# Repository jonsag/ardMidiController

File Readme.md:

# ardMidiController

## Links

### theMidinator

[YouTube](https://www.youtube.com/watch?v=JZ5yPdoPooU)  
[GitHub](https://github.com/SwitchAndLever/theMIDInatorxxx)

### SimpleSynth

### dolcewang

[Instructables](https://www.instructables.com/DIY-USB-Midi-Controller-With-Arduino-a-Beginners-G/)

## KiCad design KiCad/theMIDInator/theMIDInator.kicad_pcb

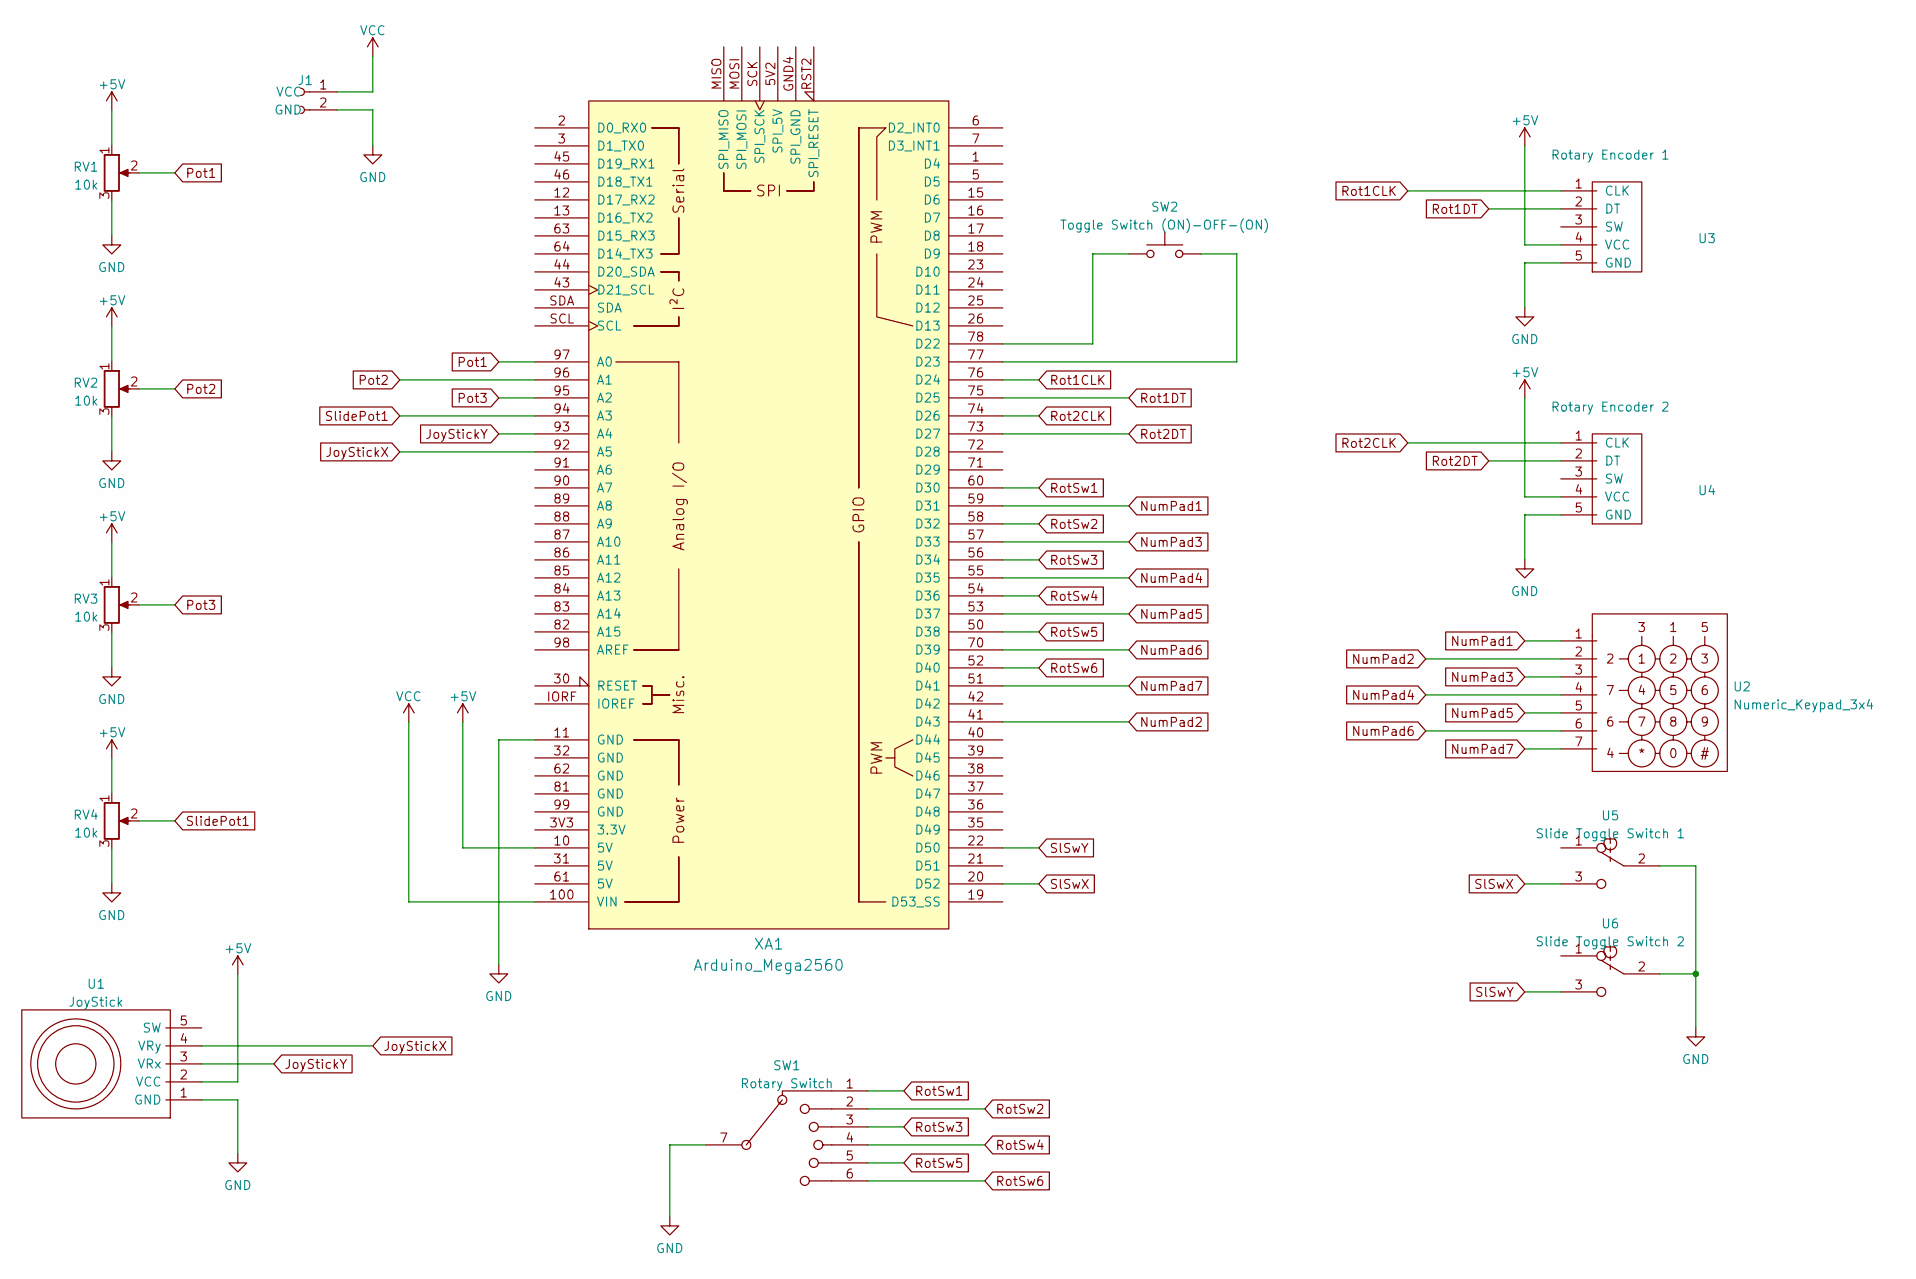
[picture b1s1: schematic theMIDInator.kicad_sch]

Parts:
J1: 2-pin_power_input_header
RV1, RV2, RV3, RV4: 10k; 3-pin JST Potentiometer
SW1: Rotary Switch; 7-pin JST Rotary Switch 1x6
SW2: Toggle Switch (ON)-OFF-(ON); 2-pin JST Switch
U1: JoyStick; 5-pin JST KY-023 JoyStick
U2: Numeric_Keypad_3x4; 7-pin JST Numeric Keypad
U3: Rotary Encoder 1; 5-pin JST Rotary Encoder
U4: Rotary Encoder 2; 5-pin JST Rotary Encoder
U5: Slide Toggle Switch 1; 3-pin JST Toggle Switch
U6: Slide Toggle Switch 2; 3-pin JST Toggle Switch
XA1: Arduino_Mega2560; Arduino_Mega2560_Shield__no_ICSP_no_mount-holes_large

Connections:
+5V: RV1.1, RV2.1, RV3.1, RV4.1, U1.2 (VCC), U3.4 (VCC), U4.4 (VCC), XA1.10 (5V)
GND: J1.2 (GND), RV1.3, RV2.3, RV3.3, RV4.3, SW1.7, U1.1 (GND), U3.5 (GND), U4.5 (GND), U5.2 (Com), U6.2 (Com), XA1.11 (GND)
JoyStickX: U1.4 (VRy), XA1.92 (A5)
JoyStickY: U1.3 (VRx), XA1.93 (A4)
unnamed: SW2.1, XA1.78 (D22)
unnamed: SW2.2, XA1.77 (D23)
NumPad1: U2.1, XA1.59 (D31)
NumPad2: U2.2, XA1.41 (D43)
NumPad3: U2.3, XA1.57 (D33)
NumPad4: U2.4, XA1.55 (D35)
NumPad5: U2.5, XA1.53 (D37)
NumPad6: U2.6, XA1.70 (D39)
NumPad7: U2.7, XA1.51 (D41)
Pot1: RV1.2, XA1.97 (A0)
Pot2: RV2.2, XA1.96 (A1)
Pot3: RV3.2, XA1.95 (A2)
Rot1CLK: U3.1 (CLK), XA1.76 (D24)
Rot1DT: U3.2 (DT), XA1.75 (D25)
Rot2CLK: U4.1 (CLK), XA1.74 (D26)
Rot2DT: U4.2 (DT), XA1.73 (D27)
RotSw1: SW1.1, XA1.60 (D30)
RotSw2: SW1.2, XA1.58 (D32)
RotSw3: SW1.3, XA1.56 (D34)
RotSw4: SW1.4, XA1.54 (D36)
RotSw5: SW1.5, XA1.50 (D38)
RotSw6: SW1.6, XA1.52 (D40)
SlSwX: U5.3 (NO), XA1.20 (D52)
SlSwY: U6.3 (NO), XA1.22 (D50)
SlidePot1: RV4.2, XA1.94 (A3)
VCC: J1.1 (VCC), XA1.100 (VIN)

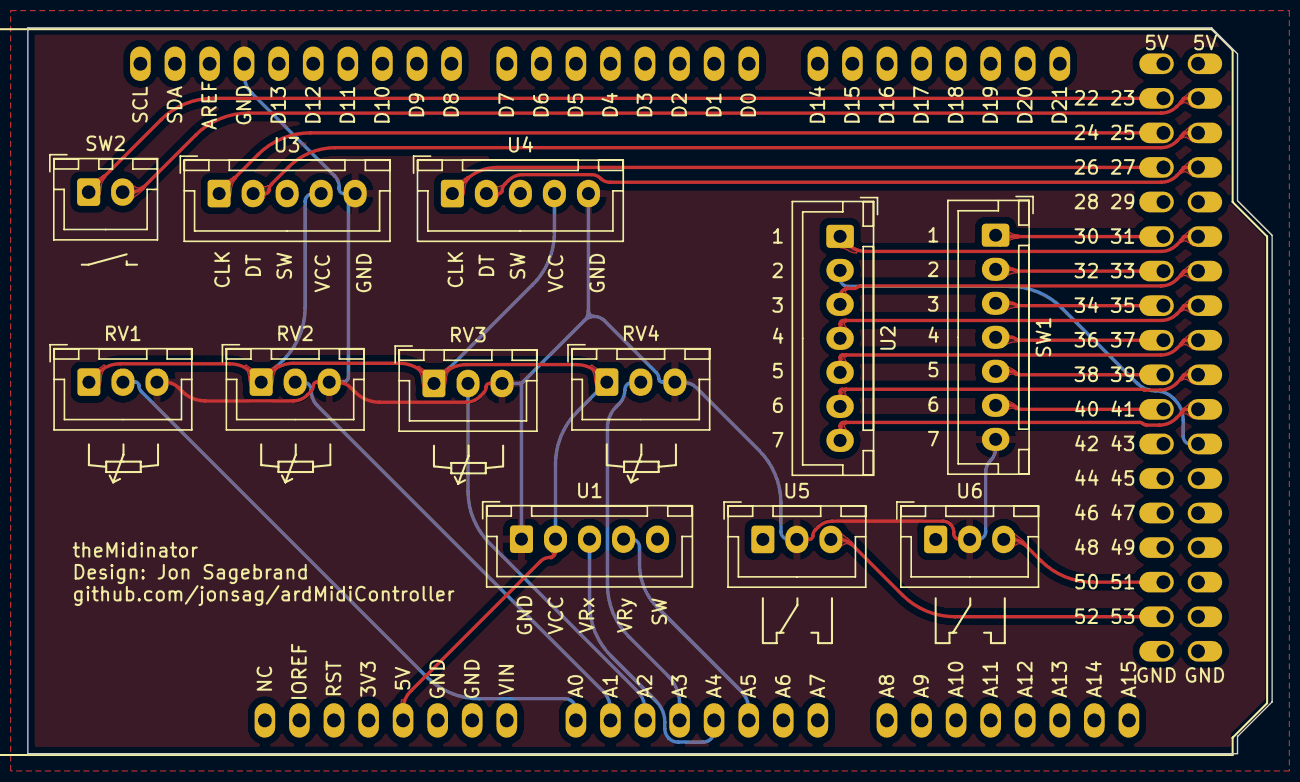
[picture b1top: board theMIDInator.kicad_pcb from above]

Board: 2 copper layers, 91.4 x 53.3 mm, 13 parts (0 on the bottom side), 29 nets.

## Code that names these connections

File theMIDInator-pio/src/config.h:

// KEYPAD //
#include <Keypad.h>

#define ROWS 4 // four rows
#define COLS 3 // three columns

char keys[ROWS][COLS] = { // keypad keys, 1-9, 0, S for star (asterisk) and P for pound (square)
    {'1', '2', '3'},
    {'4', '5', '6'},
    {'7', '8', '9'},
    {'S', '0', 'P'}};

byte rowPins[ROWS] = {43, 41, 39, 35}; // keypad row pinouts
byte colPins[COLS] = {33, 31, 37};     // keypad column pinouts

Keypad kpd = Keypad(makeKeymap(keys), rowPins, colPins, ROWS, COLS);

int midC = 60; // MIDI note value for middle C on a standard keyboard

#define transposePin1 22 // pins for the switch controlling transposing
#define transposePin2 23

int transpose = 0; // if = 0 no transposing
int transposeLeft = 0;
int transposeRight = 0;
int oldTransposeLeft = 0;
int oldTransposeRight = 0;
unsigned long transposeTimer = 0; // for debouncing

// ROTARY ENCODERS //
#define ENCODER_DO_NOT_USE_INTERRUPTS
#include <Encoder.h>

Encoder myEnc1(26, 27);
Encoder myEnc2(24, 25);

long position1 = -999;
long position2 = -999;
int encVals[12] = {64, 64, 64, 64, 64, 64, 64, 64, 64, 64, 64, 64}; // set initial value of encoder to mid range of 0-127

// ROTARY SWITCH //
#define rotSwitch1 30 // rotary switch pins
#define rotSwitch2 32
#define rotSwitch3 34
#define rotSwitch4 36
#define rotSwitch5 38
#define rotSwitch6 40

int cVal = 1;

// POTENTIOMETERS //
#define pot1 A0 // potentiometer pins
#define pot2 A1
#define pot3 A2
#define slidePot A3

int potVal1 = 0;
int potVal2 = 0;
int potVal3 = 0;
int slidePotVal = 0;

int lastPotVal1 = 0;
int lastPotVal2 = 0;
int lastPotVal3 = 0;
int lastSlidePotVal = 0;

// JOYSTICK //
#define joyX A5 // joystick pins
#define joyY A4

#define Xswitch 52 // axis switch pins
#define Yswitch 50

int joyXval = 0;
int joyYval = 0;
int lastJoyXval = 0;
int lastJoyYval = 0;

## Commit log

2022-06-21 second commit
2022-06-22 some more and some modifeide code
2022-06-22 readme
